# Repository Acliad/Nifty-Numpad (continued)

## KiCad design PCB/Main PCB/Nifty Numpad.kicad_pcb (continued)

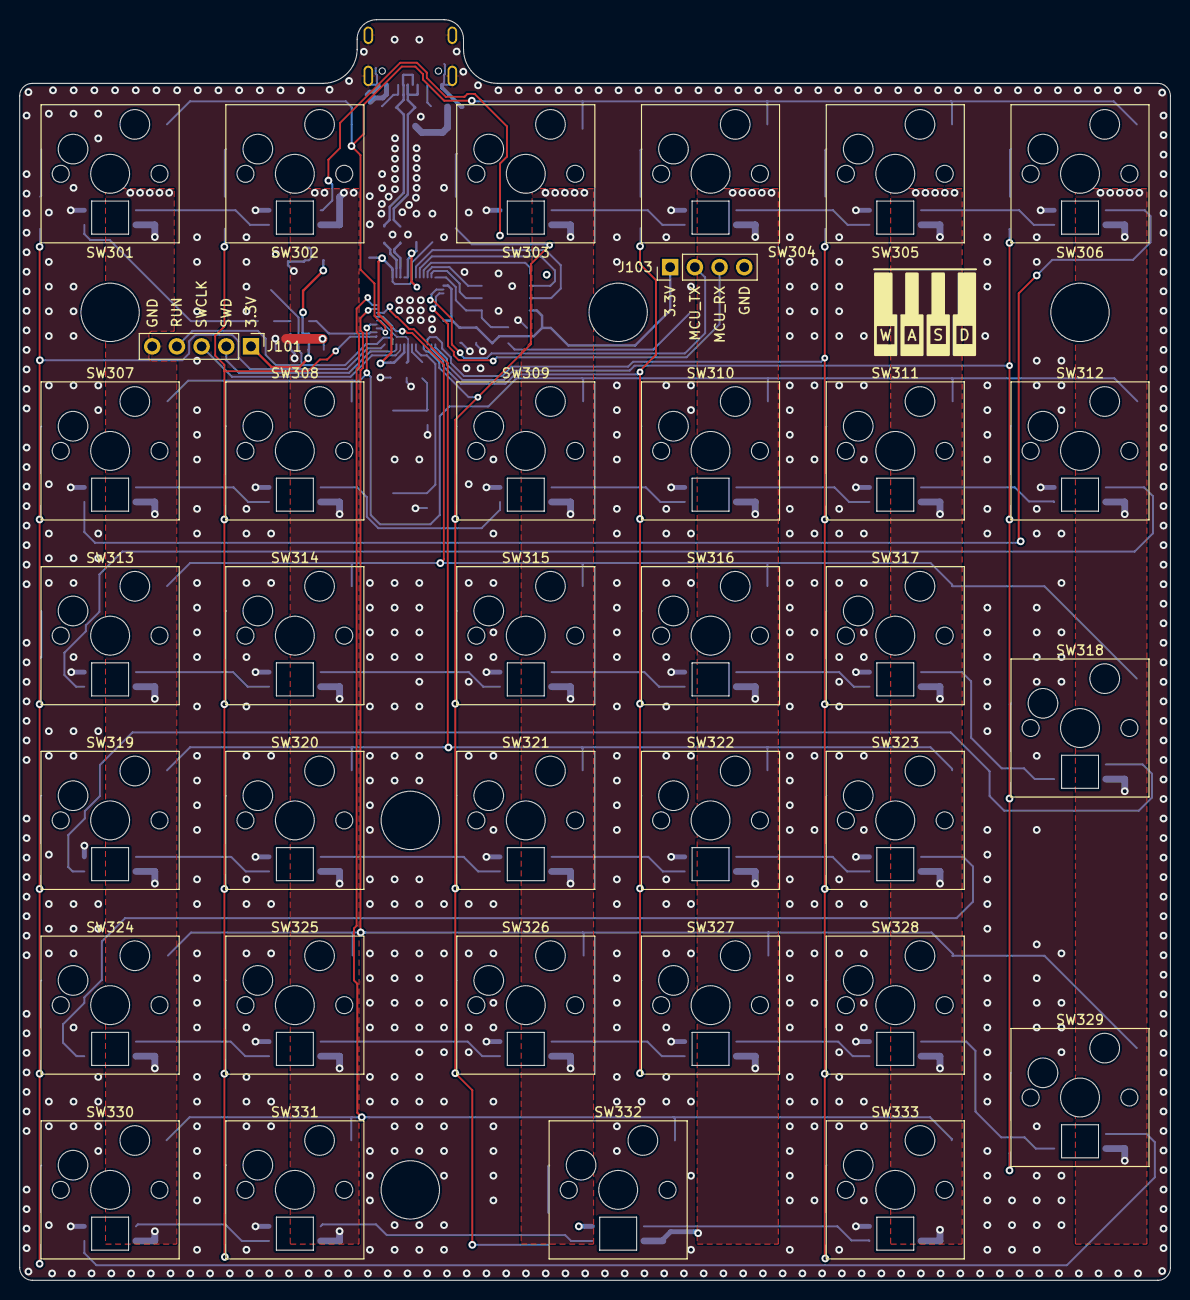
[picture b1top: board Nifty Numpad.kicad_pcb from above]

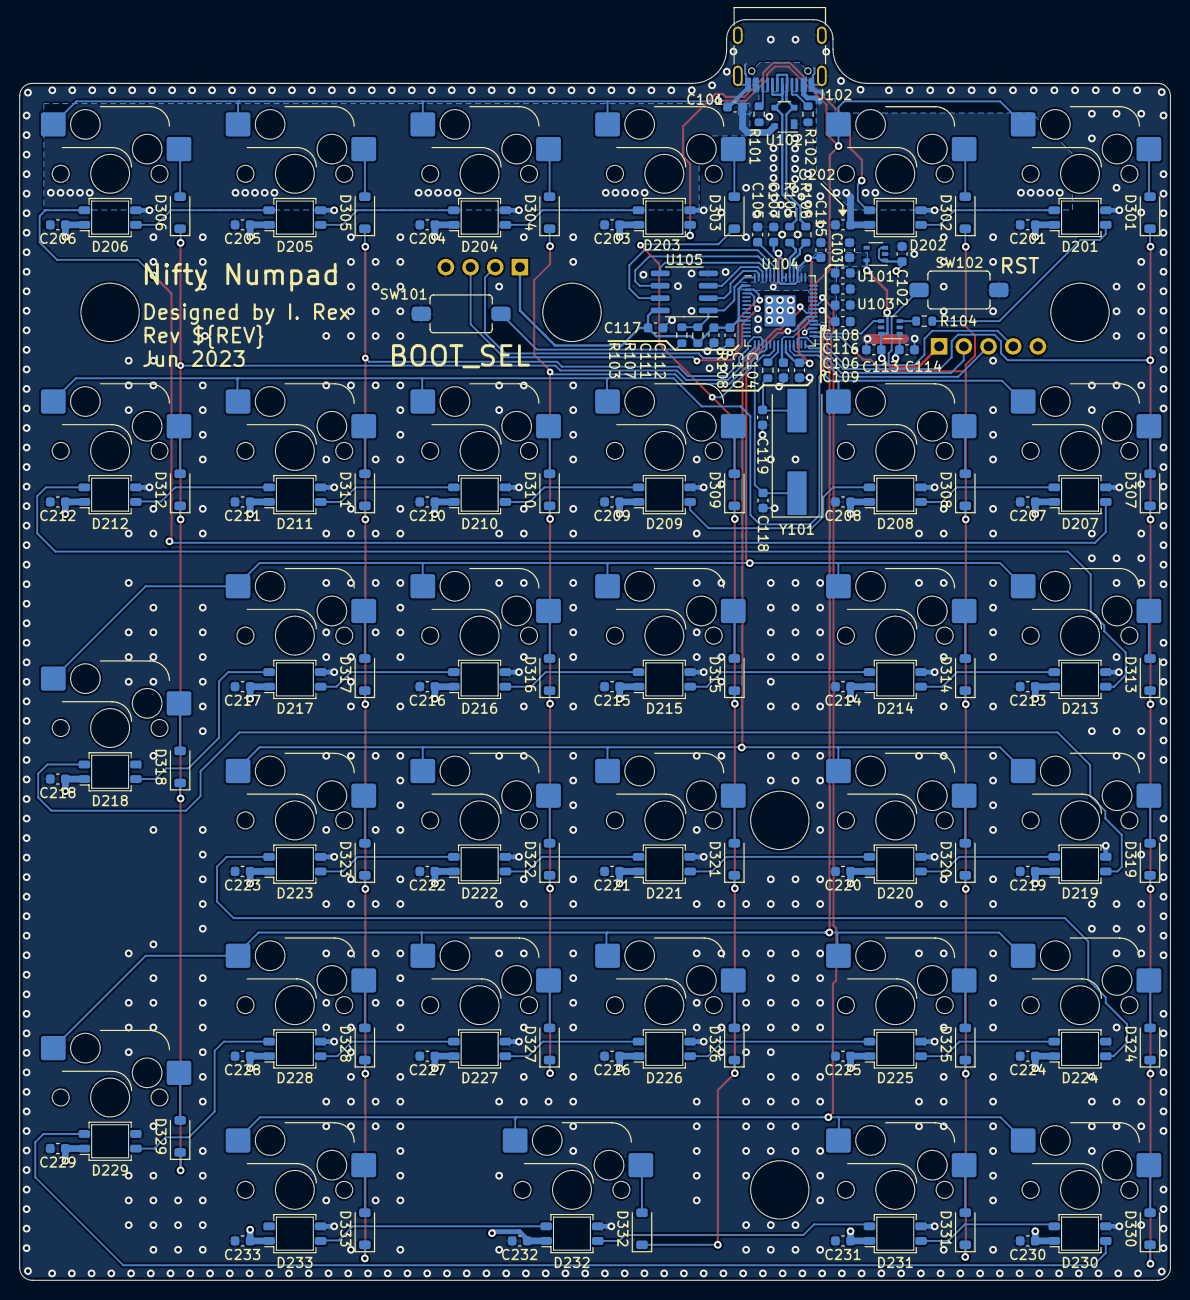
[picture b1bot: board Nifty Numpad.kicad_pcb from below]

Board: 2 copper layers, 118.4 x 129.7 mm, 175 parts (135 on the bottom side), 105 nets.

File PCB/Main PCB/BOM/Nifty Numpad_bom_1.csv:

References,Value,LCSC,DigiKey PN,Quantity Per PCB,Footprint,Datasheet
C118-C119,27pF,C107045,1276-2247-1-ND,2,C_0603_1608Metric,~
"C104-C114,  C117,  C201-C233",100nF,C14663,1276-1006-1-ND,45,C_0603_1608Metric,~
"C102-C103,  C115-C116",1uF,C15849,1276-6524-1-ND,4,C_0603_1608Metric,~
C101,10uF,C19702,490-10475-1-ND,1,C_0603_1608Metric,~
D301-D333,1N4148,C444720,4530-1N4148WCT-ND,33,D_SOD-123,https://media.digikey.com/pdf/Data%20Sheets/Anbon%20Semi%20P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
D201-D233,SK6805MINI-E,C5149201,1528-4960-ND,33,LED_SK6812-E_3.2x2.8mm,https://cdn-shop.adafruit.com/product-files/4960/4960_SK6812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
J101,SWD,C492404,2057-PH1-05-UA-ND,1 (DNF),PinHeader_1x05_P2.54mm_Vertical,~
J103,UART,C2691448,2057-PH1-04-UA-ND,1 (DNF),PinHeader_1x04_P2.54mm_Vertical,~
J102,USB-C,C2927038,2073-USB4105-GF-A-060CT-ND,1,USB_C_Receptacle_GCT_USB4105-GF-A-060,https://www.usb.org/sites/default/files/documents/usb_type-c.zip
R105-R106,27,C25190,CR0603-FX-27R0ELFCT-ND,2,R_0603_1608Metric,~
R104,330,C23138,CR0603-FX-3300ELFCT-ND,1,R_0603_1608Metric,~
R103,1k,C21190,RNCP0603FTD1K00CT-ND,1 (DNF),R_0603_1608Metric,~
R108,1k,C21190,RNCP0603FTD1K00CT-ND,1,R_0603_1608Metric,~
R101-R102,5.1k,C23186,CR0603-FX-5101ELFCT-ND,2,R_0603_1608Metric,~
R107,10k,C25804,RNCP0603FTD1K00CT-ND,1,R_0603_1608Metric,~
"SW301-SW317,  SW319-SW328,  SW330-SW331,  SW333",PG1511,C5156480,,30,SW_Hotswap_Kailh_MX_1.00u,https://www.kailhswitch.com/Content/upload/pdf/202215927/CPG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
"SW318,  SW329",PG1511,C5156480,,2,SW_Hotswap_Kailh_MX_2.00u_90deg,https://www.kailhswitch.com/Content/upload/pdf/202215927/CPG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
SW332,PG1511,C5156480,,1,SW_Hotswap_Kailh_MX_2.00u,https://www.kailhswitch.com/Content/upload/pdf/202215927/CPG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
SW101-SW102,PTS636 SL43 SMTR LFS,C2800576,CKN12309-1-ND,2 (DNF),SW-PUSH-6x3.5mm_CK-PTS636SL43x_HandSolder,https://www.ckswitches.com/media/2779/pts636.pdf
U101,3.3V,C431682,576-3215-1-ND,1,SOT-353_SC-70-5,http://ww1.microchip.com/downloads/en/DeviceDoc/mic5365.pdf
U102,CM1213A−02Sx,C5359995,CM1213A-02SROSCT-ND,1,SOT-143,https://www.onsemi.com/pdf/datasheet/cm1213a-d.pdf
U104,RP2040,C2040,2648-SC0914(13)CT-ND,1,QFN-56-1EP_7x7mm_P0.4mm_EP3.2x3.2mm,https://datasheets.raspberrypi.com/rp2040/rp2040-datasheet.pdf
U103,SN74LVC1T45DCK,C9382,31-74LVC1T45DW-7CT-ND,1,SOT-363_SC-70-6,http://www.ti.com/lit/ds/symlink/sn74lvc1t45.pdf
U105,W25Q40CLSNIG,C2641149,W25Q40CLSNIG-ND,1,SOIC-8_3.9x4.9mm_P1.27mm,http://www.winbond.com/resource-files/w25q32jv%20revg%200327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
Y101,ABLS-12.000MHZ-B4-T,C596818,535-10218-1-ND,1,Crystal_SMD_HC49-SD,https://abracon.com/Resonators/ABLS.pdf

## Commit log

2023-07-28 Moved signature to inside base and added shadow line between top and base
2023-07-30 Fixed LED rotation, beefed up standoffs, added docs
2023-07-30 Moved readme.md to the project root
2023-08-06 Added license
2023-10-07 Added PCB files for the mounting plate
2023-10-07 Updated plate to use pan head instead of flathead screws
2023-10-07 Cleaned up file placement and updated readme
2023-10-07 Updated qmk_firmware submodule
